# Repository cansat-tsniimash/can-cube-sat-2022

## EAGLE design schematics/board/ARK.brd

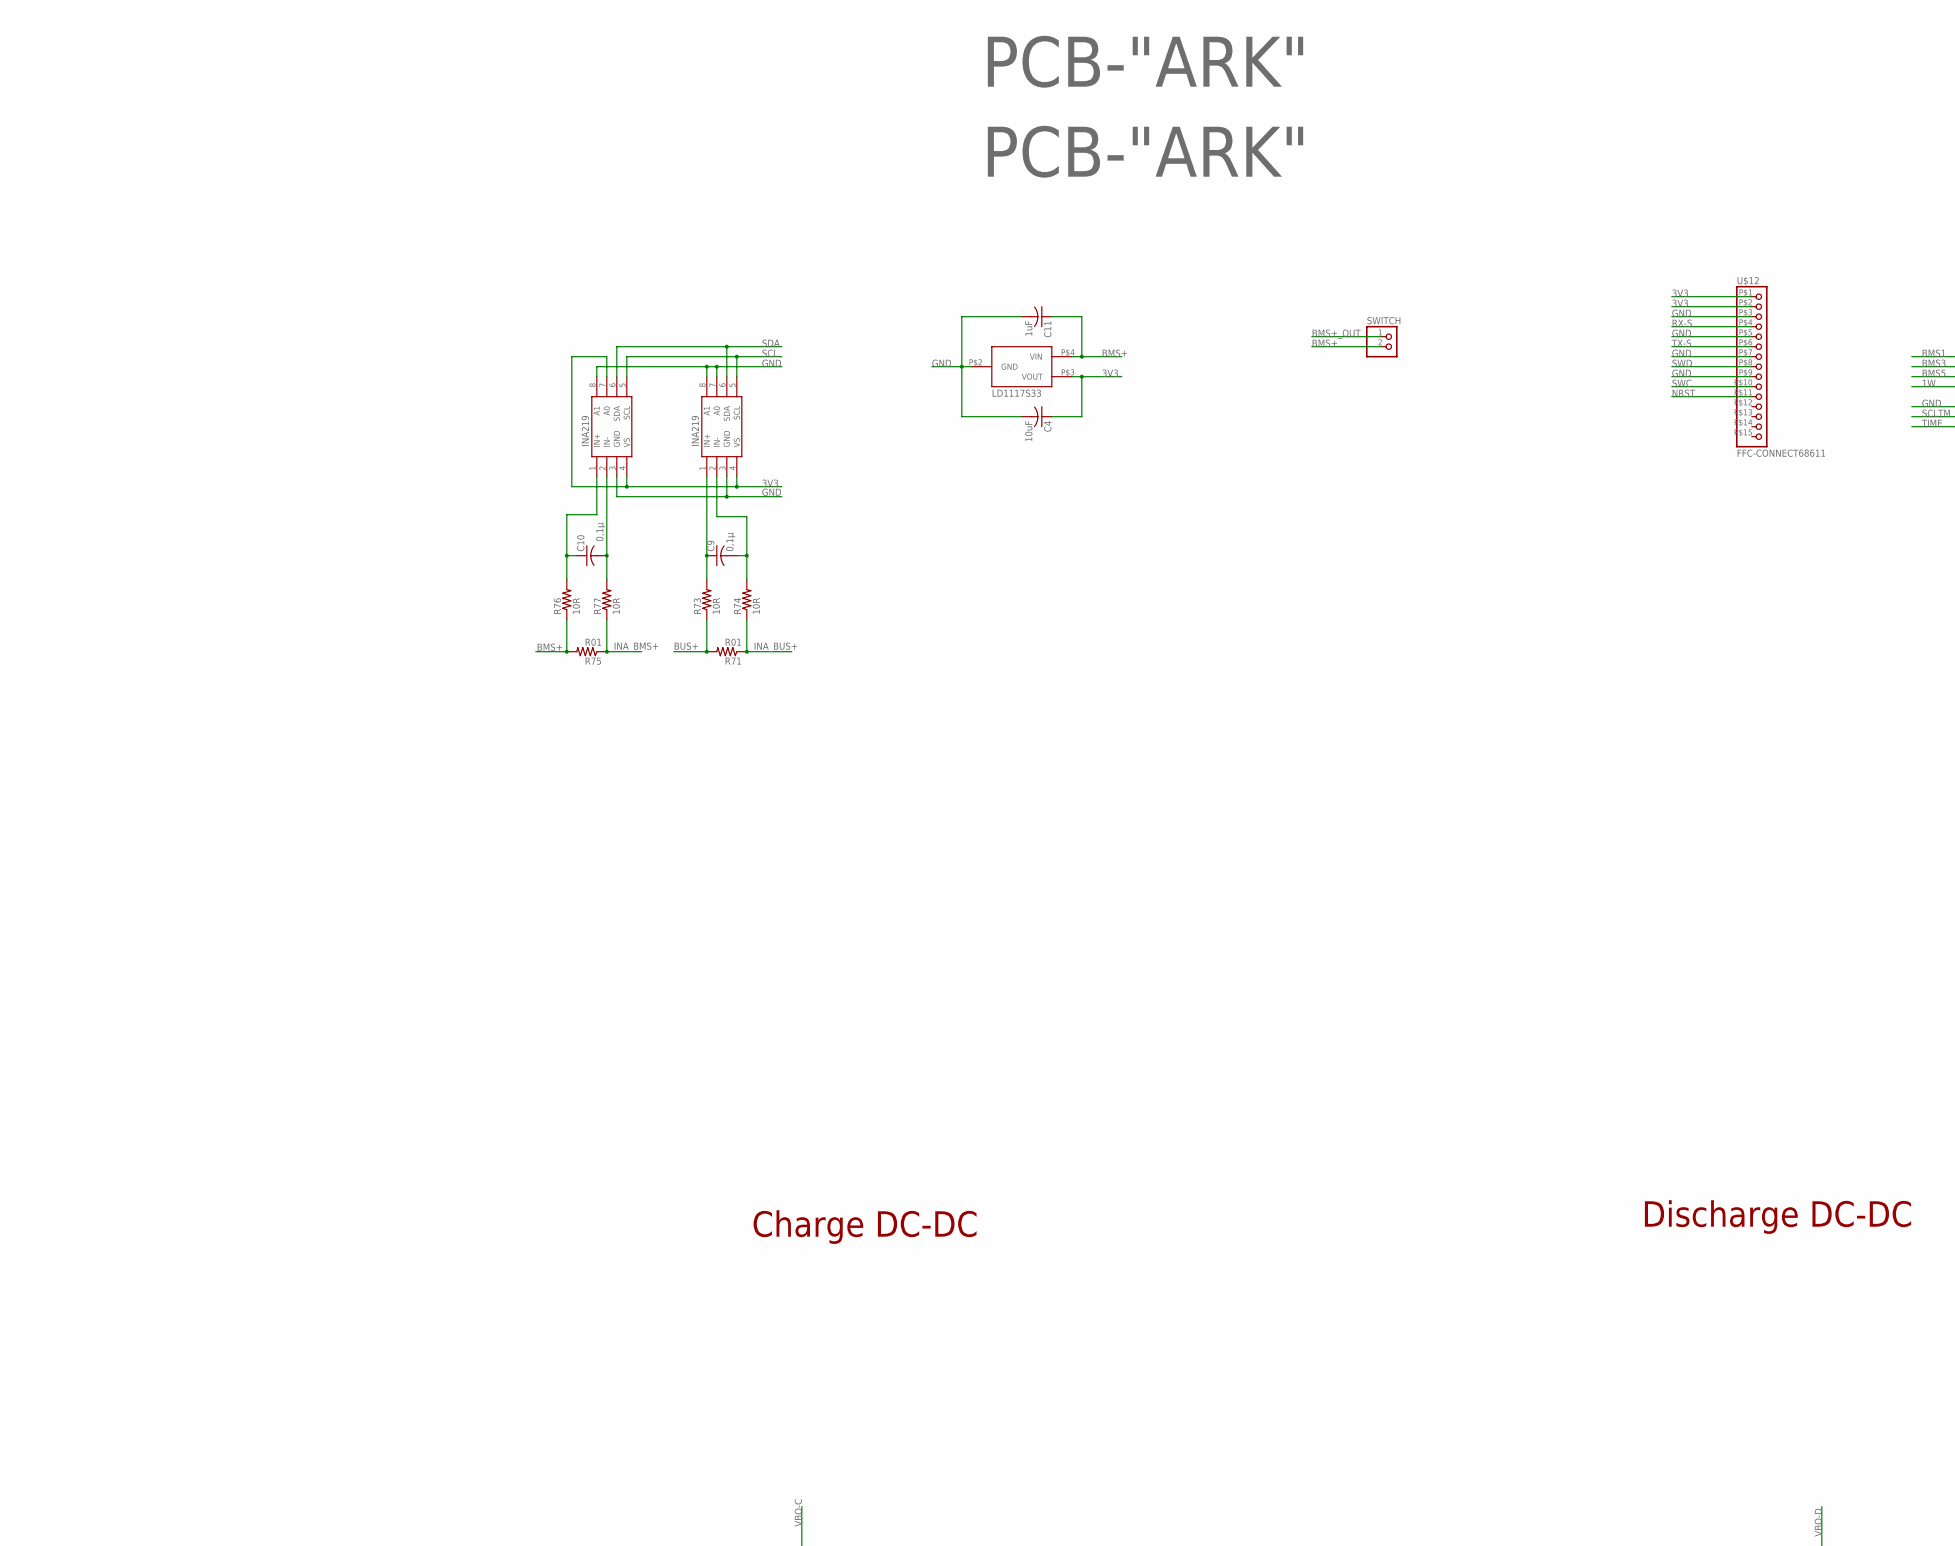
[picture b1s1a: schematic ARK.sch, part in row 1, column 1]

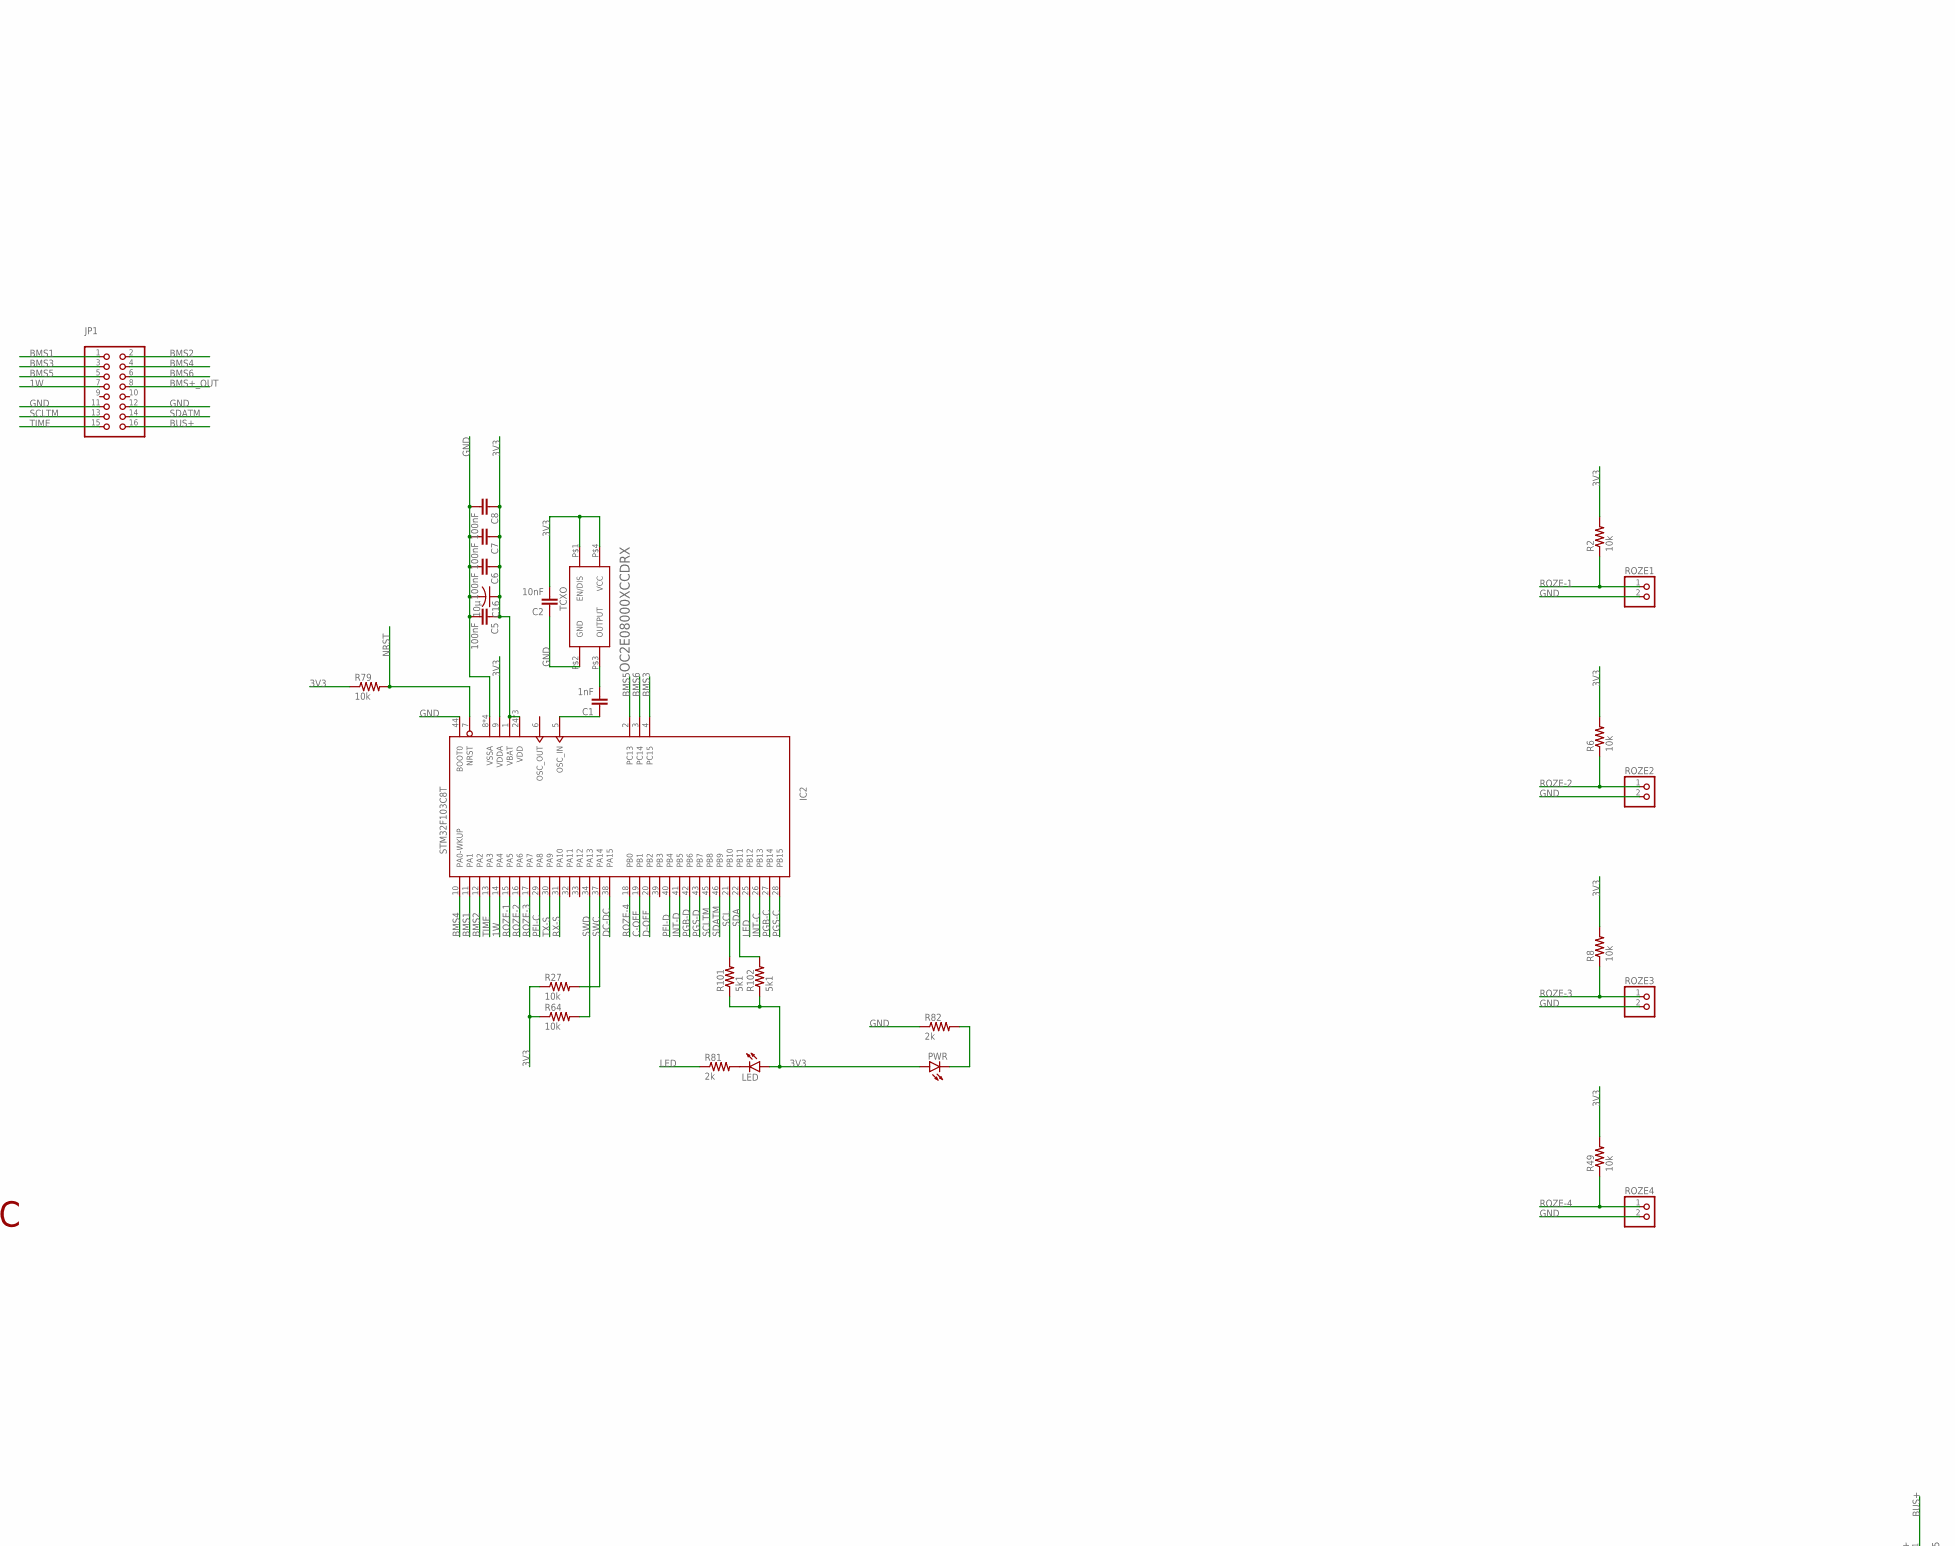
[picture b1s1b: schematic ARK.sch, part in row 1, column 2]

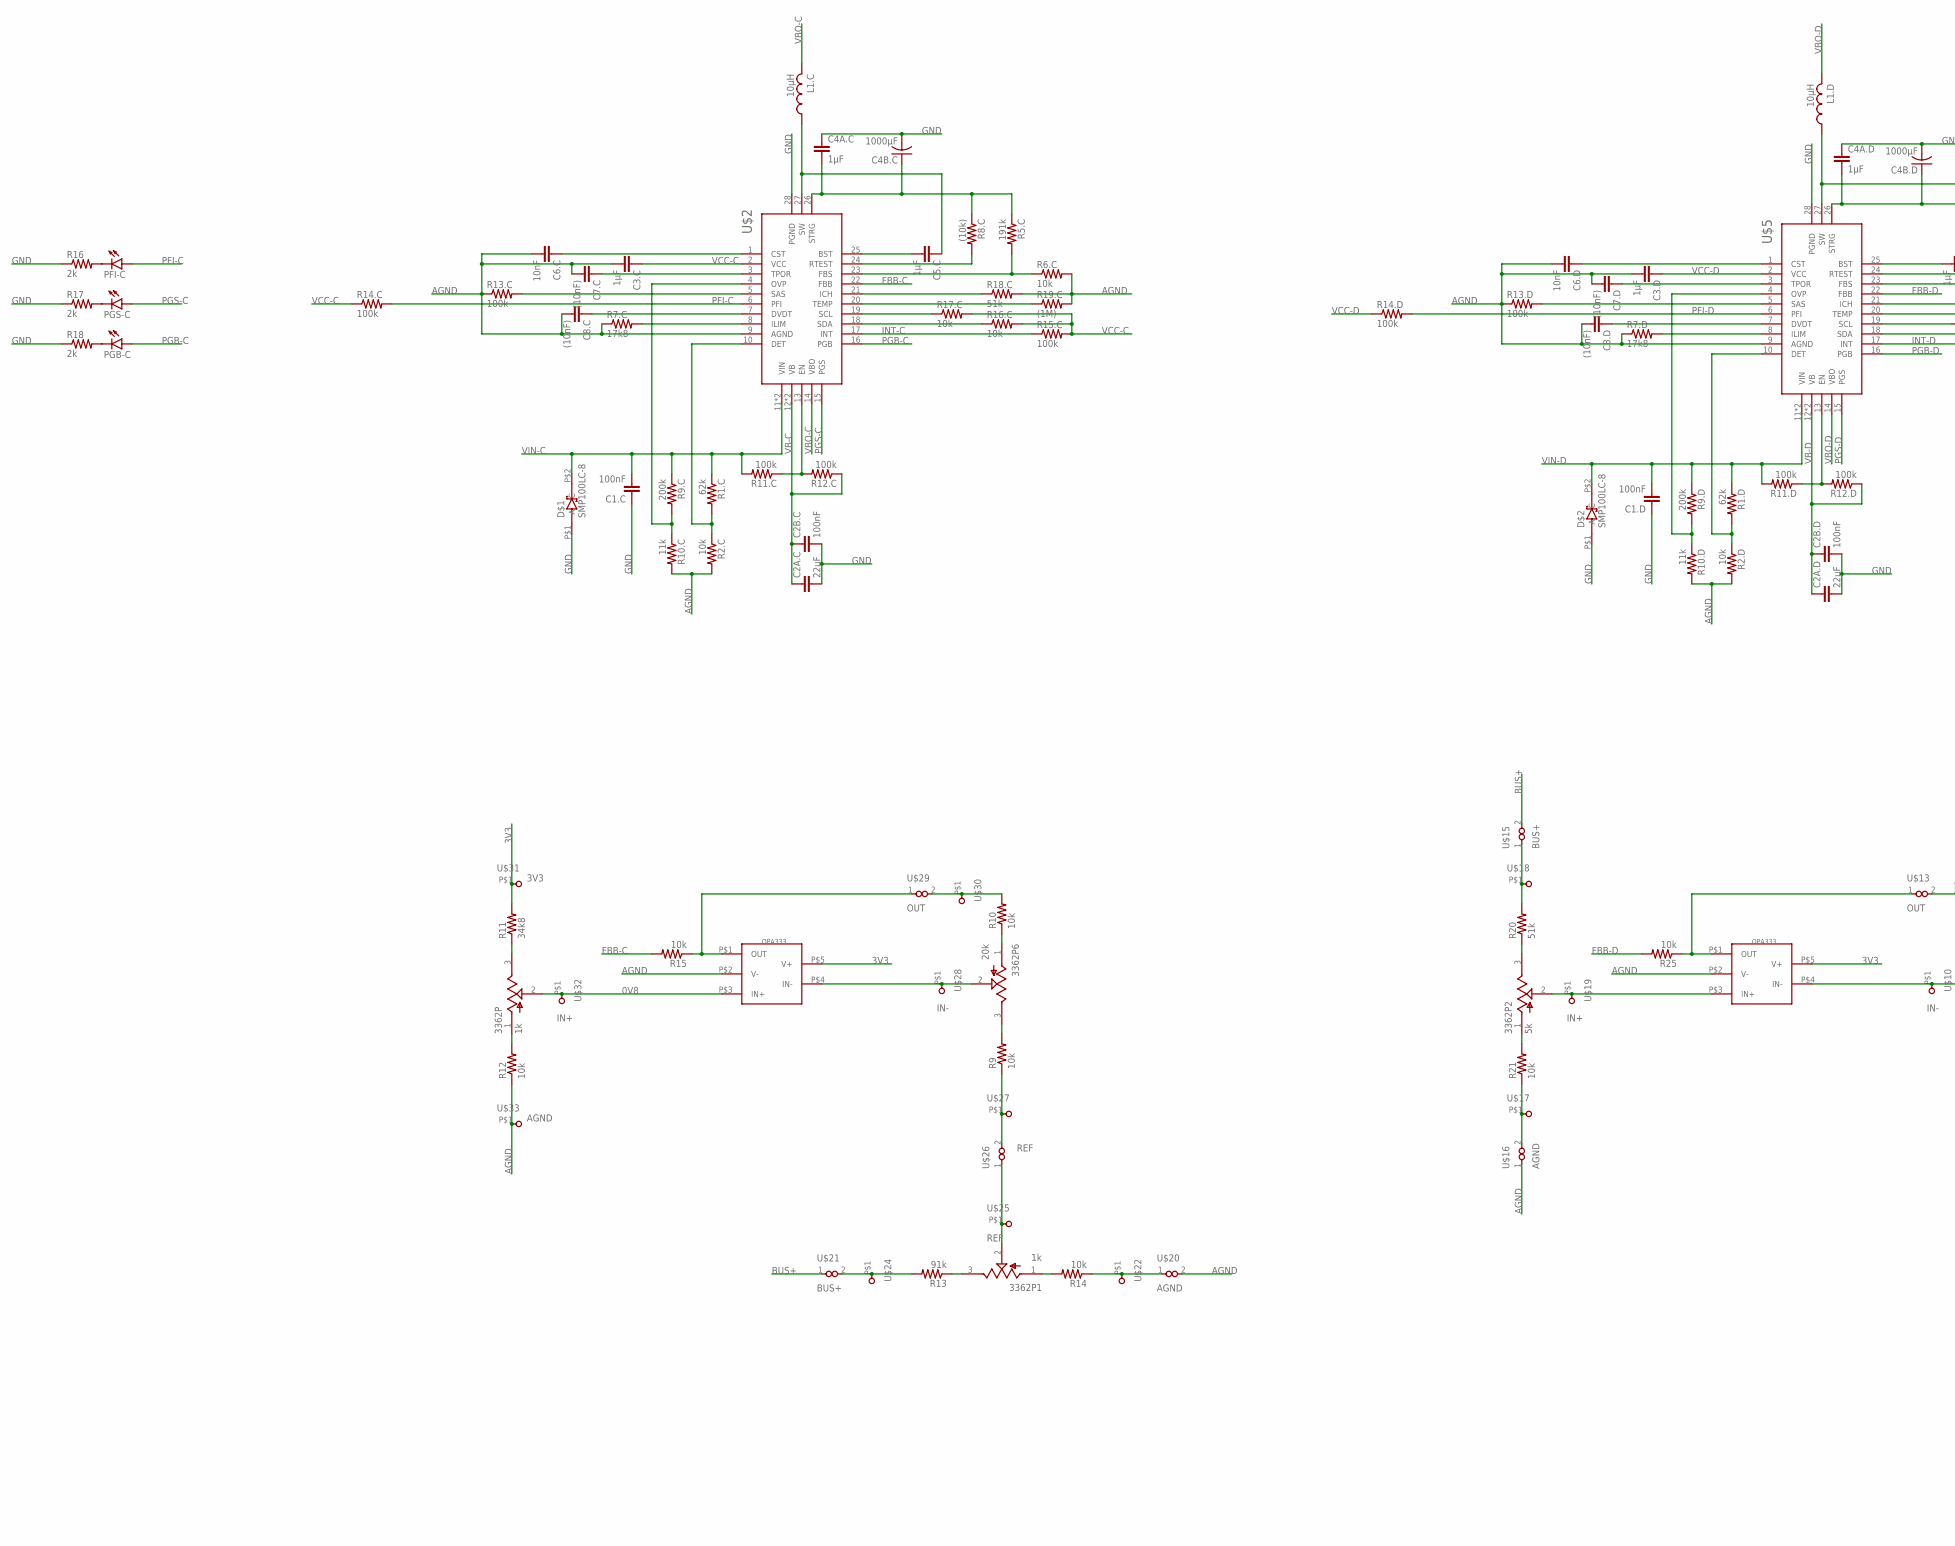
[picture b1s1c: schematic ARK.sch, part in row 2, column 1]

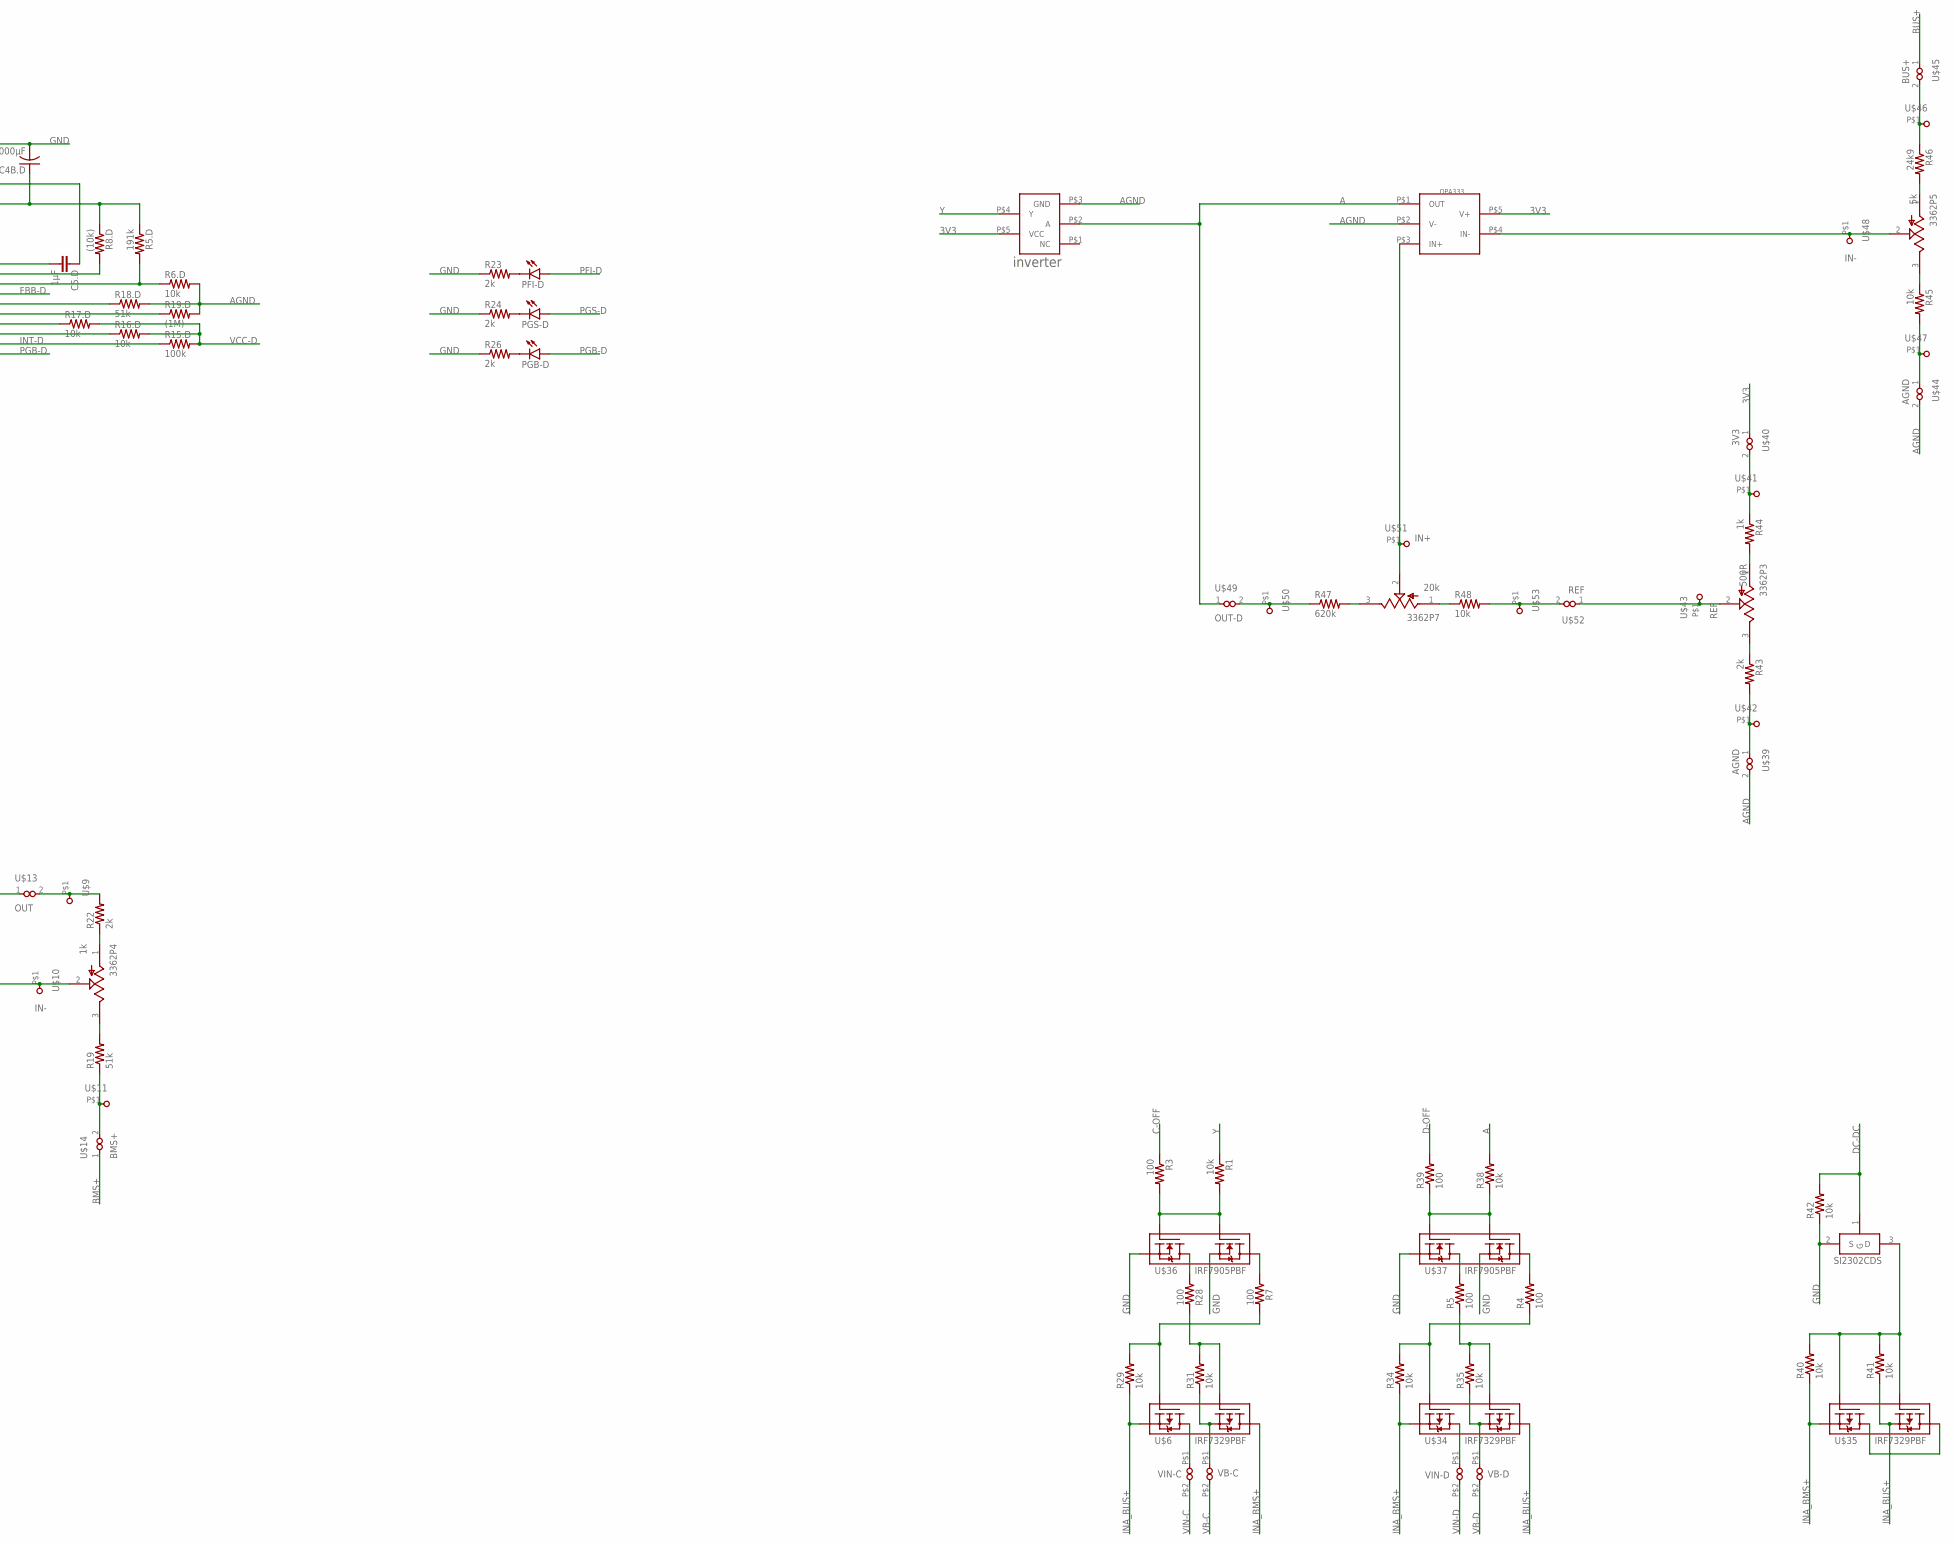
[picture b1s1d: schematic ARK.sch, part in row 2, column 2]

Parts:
3362P, 3362P1, 3362P4: 1k; TRIM_3362P-1-502LF
3362P2, 3362P5: 5k; TRIM_3362P-1-502LF
3362P3: 500R; TRIM_3362P-1-502LF
3362P6, 3362P7: 20k; TRIM_3362P-1-502LF
C1: 1nF; C0603
C1.C, C1.D, C2B.C, C2B.D, C5, C6, C7, C8: 100nF; C0603
C2, C6.C, C6.D: 10nF; C0603
C2A.C, C2A.D: 22µF; C1206
C3.C, C3.D, C5.C, C5.D: 1µF; C0603
C4: 10uF; ECAP-SMD-D4
C4A.C, C4A.D: 1µF; C1206
C4B.C, C4B.D: 1000µF; ECAP1000-CMD
C7.C, C7.D, C8.C, C8.D: (10nF); C0603
C9, C10: 0,1µ; C0603
C11: 1uF; ECAP-SMD-D4
C16: 10µ; C1206
D$1, D$2: SMP100LC-8; SMB
IC2: STM32F103C8T; LQFP48
INA219#1, INA219#2: INA219AID; SOT23-8
INVERT1: INVERTER.; SC70
JP1: PINHD-2X8; 2X08
L1.C, L1.D: 10µH; L_12X12
LD1117S33: LD1117S33; SOT223
LED: LEDCHIPLED_0603; CHIPLED_0603
OPA1, OPA2, OPA3: OPA333; SOT23-5
PFI-C: LEDCHIPLED_0603; CHIPLED_0603
PFI-D: LEDCHIPLED_0603; CHIPLED_0603
PGB-C: LEDCHIPLED_0603; CHIPLED_0603
PGB-D: LEDCHIPLED_0603; CHIPLED_0603
PGS-C: LEDCHIPLED_0603; CHIPLED_0603
PGS-D: LEDCHIPLED_0603; CHIPLED_0603
PWR: LEDCHIPLED_0603; CHIPLED_0603
R1, R2, R2.C, R2.D, R6, R6.C, R6.D, R8, R9, R10, R12, R14, R15, R16.C, R16.D, R17.C, R17.D, R21, R25, R27, R29, R31, R34, R35, R38, R40, R41, R42, R45, R48, R49, R64, R79: 10k; R0603
R1.C, R1.D: 62k; R0603
R3, R4, R5, R7, R28, R39: 100; R0603
R5.C, R5.D: 191k; R0603
R7.C, R7.D: 17k8; R0603
R8.C, R8.D: (10k); R0603
R9.C, R9.D: 200k; R0603
R10.C, R10.D: 11k; R0603
R11: 34k8; R0603
R11.C, R11.D, R12.C, R12.D, R13.C, R13.D, R14.C, R14.D, R15.C, R15.D: 100k; R0603
R13: 91k; R0603
R16, R17, R18, R22, R23, R24, R26, R43, R81, R82: 2k; R0603
R18.C, R18.D, R19, R20: 51k; R0603
R19.C, R19.D: (1M); R0603
R44: 1k; R0603
R46: 24k9; R0603
R47: 620k; R0603
R71, R75: R01; R2512
R73, R74, R76, R77: 10R; R0603
R101, R102: 5k1; R0603
ROZE1, ROZE2, ROZE3, ROZE4: PINHD-1X2; 1X02
SWITCH: PINHD-1X2; 1X02
TCXO: OC2E08000XCCDRX
U$1: VIN-C; SOLDERING-PAD-4A
U$2, U$5: MP5515; QFN-30
U$3, U$4: PCB-"ARK"; ITS-LOGO
U$6, U$34, U$35: IRF7329PBF; SO8
U$9, U$11, U$17, U$18, U$22, U$24, U$27, U$30, U$41, U$42, U$46, U$47, U$50, U$53: VIAS
U$10, U$28, U$48: IN-; VIAS
U$12: FFC-CONNECT68611; 68611
U$13, U$29: OUT; VIAS-CONNECT
U$14: BMS+; VIAS-CONNECT
U$15, U$21, U$45: BUS+; VIAS-CONNECT
U$16, U$20, U$39, U$44: AGND; VIAS-CONNECT
U$19, U$32, U$51: IN+; VIAS
U$23: VB-C; SOLDERING-PAD-4A
U$25, U$43: REF; VIAS
U$26, U$52: REF; VIAS-CONNECT
U$31: 3V3; VIAS
U$33: AGND; VIAS
U$36, U$37: IRF7905PBF; SO8
U$38: SI2302CDS; SOT23-3
U$40: 3V3; VIAS-CONNECT
U$49: OUT-D; VIAS-CONNECT
U$54: VIN-D; SOLDERING-PAD-4A
U$55: VB-D; SOLDERING-PAD-4A

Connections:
0V8: 3362P.2 (WIPER), OPA2.P$3 (IN+), U$32.P$1
1W: IC2.14 (PA4), JP1.7
3V3: C2.2, C4.P+ (1), C5.1, C6.1, C7.1, C8.1, C16.1, IC2.1 (VBAT), IC2.9 (VDDA), IC2.24 (VDD), IC2.36 (VDD), IC2.48 (VDD), INA219#1.4 (VS), INA219#2.4 (VS), INA219#2.7 (A0), INVERT1.P$5 (VCC), LD1117S33.P$3 (VOUT), LED.A, OPA1.P$5 (V+), OPA2.P$5 (V+), OPA3.P$5 (V+), PWR.A, R2.2, R6.2, R8.2, R11.2, R27.1, R49.2, R64.1, R79.1, R101.1, R102.1, TCXO.P$1 (EN/DIS), TCXO.P$4 (VCC), U$12.P$1 (1), U$12.P$2 (2), U$31.P$1, U$40.1
A: INVERT1.P$2 (A), OPA1.P$1 (OUT), R38.2, U$49.1
AGND: C3.C.2, C3.D.2, C6.C.2, C6.D.2, C7.C.2, C7.D.2, C8.C.2, C8.D.2, INVERT1.P$3 (GND), OPA1.P$2 (V-), OPA2.P$2 (V-), OPA3.P$2 (V-), R2.C.2, R2.D.2, R6.C.2, R6.D.2, R7.C.1, R7.D.1, R10.C.2, R10.D.2, R12.1, R13.C.1, R13.D.1, R18.C.2, R18.D.2, R19.C.2, R19.D.2, U$2.9 (AGND), U$5.9 (AGND), U$16.1, U$20.2, U$33.P$1, U$39.2, U$44.2; also elsewhere on the board
BMS1: IC2.11 (PA1), JP1.1
BMS2: IC2.12 (PA2), JP1.2
BMS3: IC2.4 (PC15), JP1.3
BMS4: IC2.10 (PA0-WKUP), JP1.4
BMS5: IC2.2 (PC13), JP1.5
BMS6: IC2.3 (PC14), JP1.6
BMS+: C11.P+ (1), LD1117S33.P$4 (VIN), R75.2, R76.1, SWITCH.2, U$14.1
BMS+_OUT: JP1.8, SWITCH.1
BUS+: JP1.16, R71.2, R73.1, U$15.2, U$21.1, U$45.1
C-OFF: IC2.19 (PB1), R3.1
D-OFF: IC2.20 (PB2), R39.2
DC-DC: IC2.38 (PA15), R42.2, U$38.1 (G)
FBB-C: R15.2, U$2.22 (FBB)
FBB-D: R25.2, U$5.22 (FBB)
GND: C1.C.1, C1.D.1, C2.1, C2A.C.2, C2A.D.2, C2B.C.2, C2B.D.2, C4.P- (2), C4A.C.1, C4A.D.1, C4B.C.P$2 (2), C4B.D.P$2 (2), C5.2, C6.2, C7.2, C8.2, C11.P- (2), C16.2, D$1.P$1 (A), D$2.P$1 (A), IC2.8 (VSSA), IC2.23 (VSSA), IC2.35 (VSSA), IC2.44 (BOOT0), IC2.47 (VSSA), INA219#1.3 (GND), INA219#1.7 (A0), INA219#1.8 (A1), INA219#2.3 (GND), INA219#2.8 (A1), JP1.11, JP1.12, LD1117S33.P$2 (GND), R16.1, R17.1, R18.1, R23.1, R24.1, R26.1, R42.1, R82.1, ROZE1.2, ROZE2.2, ROZE3.2, ROZE4.2, TCXO.P$2 (GND), U$2.28 (PGND), U$5.28 (PGND), U$12.P$3 (3), U$12.P$5 (5), U$12.P$7 (7), U$12.P$9 (9), U$36.1 (S2), U$36.3 (S1), U$37.1 (S2), U$37.3 (S1), U$38.2 (S); also elsewhere on the board
INA_BMS+: R34.1, R40.1, R75.1, R77.1, U$6.7 (D1), U$6.8 (D1), U$34.3 (S2), U$35.3 (S2)
INA_BUS+: R29.1, R41.1, R71.1, R74.1, U$6.3 (S2), U$34.7 (D1), U$34.8 (D1), U$35.1 (S1)
INT-C: IC2.26 (PB13), R15.C.1, U$2.17 (INT)
INT-D: IC2.41 (PB5), R15.D.1, U$5.17 (INT)
LED: IC2.25 (PB12), R81.1
unnamed: C1.1, IC2.5 (OSC_IN)
unnamed: U$1.P$1 (1), U$6.5 (D2), U$6.6 (D2)
unnamed: R31.1, U$6.1 (S1), U$23.P$1 (1)
unnamed: C1.2, TCXO.P$3 (OUTPUT)
unnamed: R4.1, R34.2, U$34.4 (G2)
unnamed: OPA3.P$1 (OUT), R25.1, U$13.1
unnamed: R11.C.1, R12.C.2, U$2.13 (EN)
unnamed: R7.C.2, U$2.8 (ILIM)
unnamed: C7.C.1, U$2.3 (TPOR)
unnamed: R1.C.2, R2.C.1, U$2.10 (DET)
unnamed: R9.C.2, R10.C.1, U$2.4 (OVP)
unnamed: C8.C.1, U$2.7 (DVDT)
unnamed: R18.C.1, U$2.21 (ICH)
unnamed: C9.2, INA219#1.2 (IN-), R74.2
unnamed: R19.C.1, U$2.20 (TEMP)
unnamed: R13.C.2, U$2.5 (SAS)
unnamed: LED.C, R81.2
unnamed: C6.C.1, U$2.1 (CST)
unnamed: C4A.C.2, C4B.C.P$1 (1), R5.C.1, R8.C.1, U$2.26 (STRG)
unnamed: C5.C.2, U$2.25 (BST)
unnamed: C5.C.1, L1.C.P$1 (1), U$2.27 (SW)
unnamed: R5.C.2, R6.C.1, U$2.23 (FBS)
unnamed: R8.C.2, U$2.24 (RTEST)
unnamed: 3362P4.1 (CCW), R22.1
unnamed: R7.2, R29.2, U$6.4 (G2)
unnamed: R17.C.1, U$2.19 (SCL)
unnamed: R16.C.1, U$2.18 (SDA)
unnamed: R5.1, R35.2, U$34.2 (G1)
unnamed: 3362P2.2 (WIPER), OPA3.P$3 (IN+), U$19.P$1
unnamed: R11.D.1, R12.D.2, U$5.13 (EN)
unnamed: R1.D.2, R2.D.1, U$5.10 (DET)
unnamed: R9.D.2, R10.D.1, U$5.4 (OVP)
unnamed: R7.D.2, U$5.8 (ILIM)
unnamed: C7.D.1, U$5.3 (TPOR)
unnamed: C8.D.1, U$5.7 (DVDT)
unnamed: R18.D.1, U$5.21 (ICH)
unnamed: R19.D.1, U$5.20 (TEMP)
unnamed: R13.D.2, U$5.5 (SAS)
unnamed: C6.D.1, U$5.1 (CST)
unnamed: C5.D.2, U$5.25 (BST)
unnamed: C5.D.1, L1.D.P$1 (1), U$5.27 (SW)
unnamed: R5.D.2, R6.D.1, U$5.23 (FBS)
unnamed: R8.D.2, U$5.24 (RTEST)
unnamed: C4A.D.2, C4B.D.P$1 (1), R5.D.1, R8.D.1, U$5.26 (STRG)
unnamed: U$35.5 (D2), U$35.6 (D2), U$35.7 (D1), U$35.8 (D1)
unnamed: R17.D.1, U$5.19 (SCL)
unnamed: R1.2, R3.2, U$36.2 (G2), U$36.4 (G1)
unnamed: R16.D.1, U$5.18 (SDA)
unnamed: U$34.5 (D2), U$34.6 (D2), U$54.P$1 (1)
unnamed: R38.1, R39.1, U$37.2 (G2), U$37.4 (G1)
unnamed: OPA2.P$1 (OUT), R15.1, U$29.1
unnamed: 3362P6.2 (WIPER), OPA2.P$4 (IN-), U$28.P$1
unnamed: 3362P6.3 (CW), R9.2
unnamed: 3362P6.1 (CCW), R10.1
unnamed: PFI-C.C, R16.2
unnamed: 3362P.3 (CW), R11.1
unnamed: 3362P.1 (CCW), R12.2
unnamed: 3362P1.3 (CW), R13.1
unnamed: 3362P1.1 (CCW), R14.2
unnamed: 3362P1.2 (WIPER), U$25.P$1, U$26.1
unnamed: 3362P2.3 (CW), R20.1
unnamed: PGS-C.C, R17.2
unnamed: 3362P2.1 (CCW), R21.2
unnamed: PGB-C.C, R18.2
unnamed: 3362P4.2 (WIPER), OPA3.P$4 (IN-), U$10.P$1
unnamed: 3362P4.3 (CW), R19.2
unnamed: PFI-D.C, R23.2
unnamed: PGS-D.C, R24.2
unnamed: PGB-D.C, R26.2
unnamed: R22.2, U$9.P$1, U$13.2
unnamed: R19.1, U$11.P$1, U$14.2
unnamed: R20.2, U$15.1, U$18.P$1
unnamed: R21.1, U$16.2, U$17.P$1
unnamed: R13.2, U$21.2, U$24.P$1
unnamed: R14.1, U$20.1, U$22.P$1
unnamed: R35.1, U$34.1 (S1), U$55.P$1 (1)
unnamed: R5.2, U$37.7 (D2), U$37.8 (D2)
unnamed: R28.1, U$36.7 (D2), U$36.8 (D2)
unnamed: R4.2, U$37.5 (D1), U$37.6 (D1)
unnamed: R7.1, U$36.5 (D1), U$36.6 (D1)
unnamed: R9.1, U$26.2, U$27.P$1
unnamed: R10.2, U$29.2, U$30.P$1
unnamed: R28.2, R31.2, U$6.2 (G1)
unnamed: 3362P3.3 (CW), R43.1
unnamed: 3362P3.1 (CCW), R44.2
unnamed: 3362P3.2 (WIPER), U$43.P$1, U$52.1
unnamed: R40.2, R41.2, U$35.2 (G1), U$35.4 (G2), U$38.3 (D)
unnamed: R43.2, U$39.1, U$42.P$1
unnamed: R44.1, U$40.2, U$41.P$1
unnamed: 3362P5.3 (CW), R45.1
unnamed: 3362P5.1 (CCW), R46.2
unnamed: 3362P5.2 (WIPER), OPA1.P$4 (IN-), U$48.P$1
unnamed: R45.2, U$44.1, U$47.P$1
unnamed: R46.1, U$45.2, U$46.P$1
unnamed: 3362P7.1 (CCW), R48.1
unnamed: 3362P7.2 (WIPER), OPA1.P$3 (IN+), U$51.P$1
unnamed: 3362P7.3 (CW), R47.2
unnamed: R47.1, U$49.2, U$50.P$1
unnamed: R48.2, U$52.2, U$53.P$1
unnamed: C9.1, INA219#1.1 (IN+), R73.2
unnamed: C10.1, INA219#2.1 (IN+), R76.2
unnamed: C10.2, INA219#2.2 (IN-), R77.2
unnamed: PWR.C, R82.2
NRST: IC2.7 (NRST), R79.2, U$12.P$11 (11)
PFI-C: IC2.29 (PA8), PFI-C.A, R14.C.2, U$2.6 (PFI)
PFI-D: IC2.40 (PB4), PFI-D.A, R14.D.2, U$5.6 (PFI)
PGB-C: IC2.27 (PB14), PGB-C.A, U$2.16 (PGB)
PGB-D: IC2.42 (PB6), PGB-D.A, U$5.16 (PGB)
PGS-C: IC2.28 (PB15), PGS-C.A, U$2.15 (PGS)
PGS-D: IC2.43 (PB7), PGS-D.A, U$5.15 (PGS)
ROZE-1: IC2.15 (PA5), R2.1, ROZE1.1
ROZE-2: IC2.16 (PA6), R6.1, ROZE2.1
ROZE-3: IC2.17 (PA7), R8.1, ROZE3.1
ROZE-4: IC2.18 (PB0), R49.1, ROZE4.1
RX-S: IC2.31 (PA10), U$12.P$4 (4)
SCL: IC2.21 (PB10), INA219#1.5 (SCL), INA219#2.5 (SCL), R101.2
SCLTM: IC2.45 (PB8), JP1.13
SDA: IC2.22 (PB11), INA219#1.6 (SDA), INA219#2.6 (SDA), R102.2
SDATM: IC2.46 (PB9), JP1.14
SWC: IC2.37 (PA14), R27.2, U$12.P$10 (10)
SWD: IC2.34 (PA13), R64.2, U$12.P$8 (8)
TIME: IC2.13 (PA3), JP1.15
TX-S: IC2.30 (PA9), U$12.P$6 (6)
VB-C: C2A.C.1, C2B.C.1, R12.C.1, U$2.12 (VB), U$2.29 (VB), U$23.P$2 (2)
VB-D: C2A.D.1, C2B.D.1, R12.D.1, U$5.12 (VB), U$5.29 (VB), U$55.P$2 (2)
VBO-C: L1.C.P$2 (2), U$2.14 (VBO)
VBO-D: L1.D.P$2 (2), U$5.14 (VBO)
VCC-C: C3.C.1, R14.C.1, R15.C.2, R16.C.2, R17.C.2, U$2.2 (VCC)
VCC-D: C3.D.1, R14.D.1, R15.D.2, R16.D.2, R17.D.2, U$5.2 (VCC)
VIN-C: C1.C.2, D$1.P$2 (C), R1.C.1, R9.C.1, R11.C.2, U$1.P$2 (2), U$2.11 (VIN), U$2.30 (VIN)
VIN-D: C1.D.2, D$2.P$2 (C), R1.D.1, R9.D.1, R11.D.2, U$5.11 (VIN), U$5.30 (VIN), U$54.P$2 (2)
Y: INVERT1.P$4 (Y), R1.1

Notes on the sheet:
Charge DC-DC
Discharge DC-DC

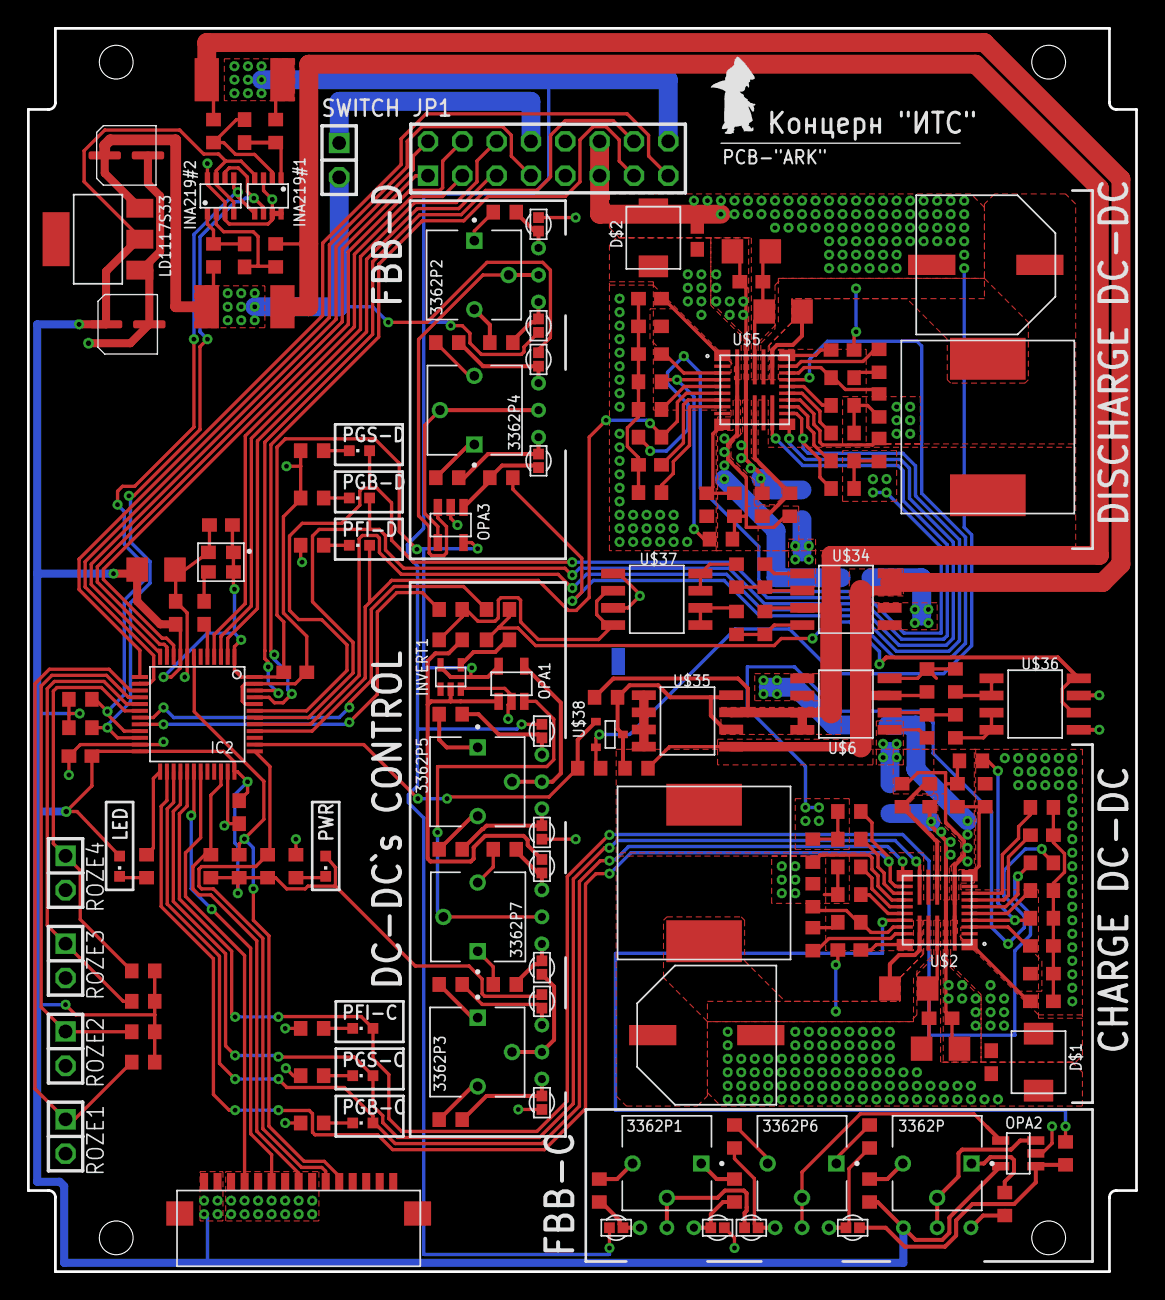
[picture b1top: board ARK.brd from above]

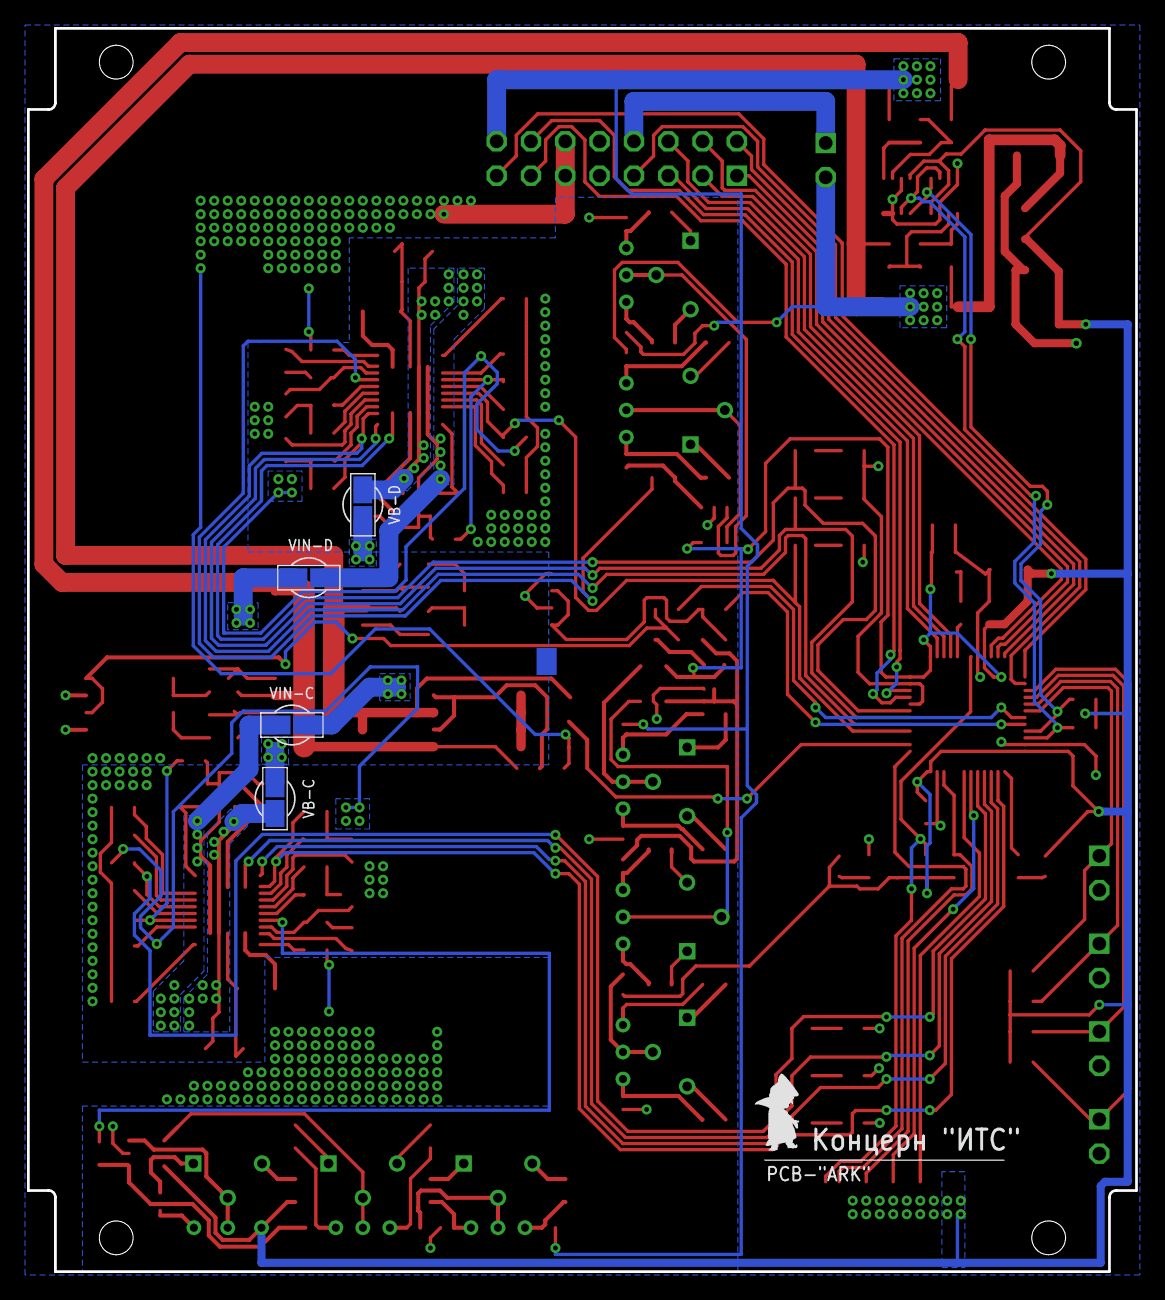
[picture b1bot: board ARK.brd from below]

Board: 2 copper layers, 82.0 x 92.0 mm, 210 parts (6 on the bottom side), 157 nets.

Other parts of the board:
U$7: GNDS-CONNECTOR

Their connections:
AGND: U$7.P$2; also elsewhere on the board
GND: U$7.P$1; also elsewhere on the board

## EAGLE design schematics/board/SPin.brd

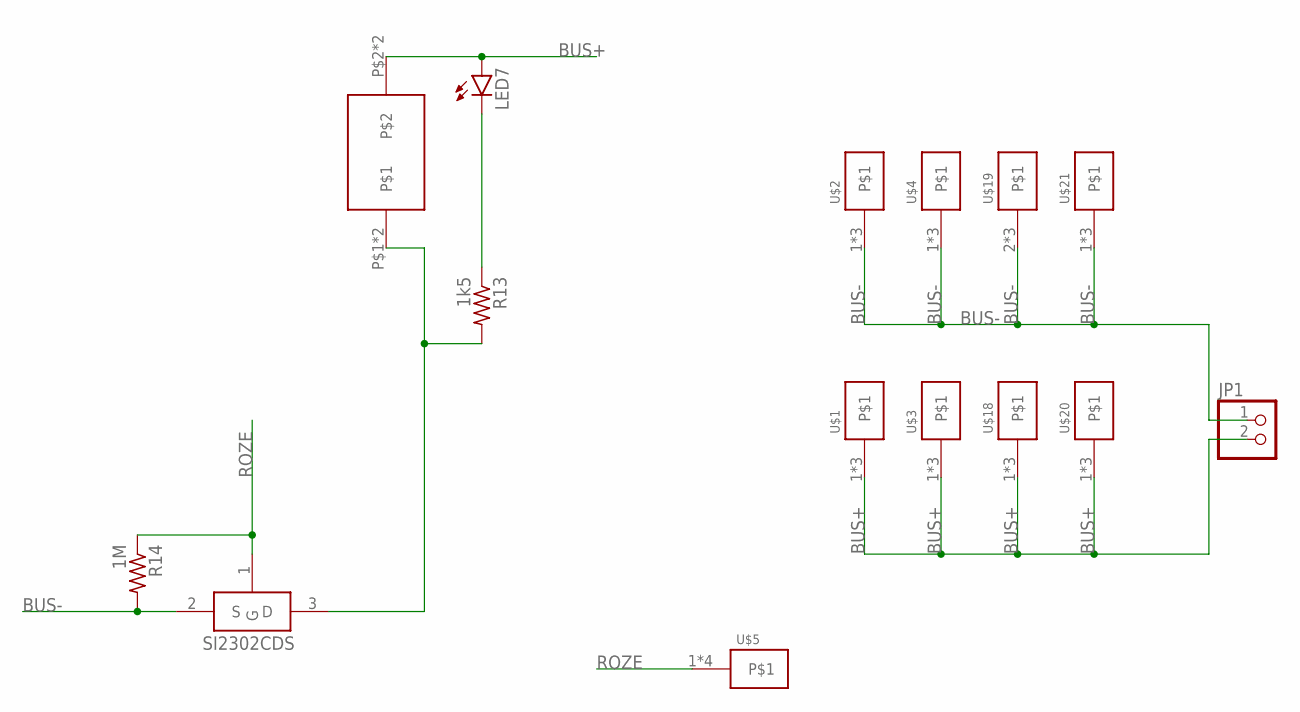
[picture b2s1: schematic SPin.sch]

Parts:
JP1: PINHD-1X2; 1X02
LED7: LEDCHIPLED_0603; CHIPLED_0603
R13: 1k5; R0603
R14: 1M; R0603
U$1, U$2, U$20, U$21: KCONNECT3; KCONNECT-3
U$3, U$4, U$18: KCONNECT4; KCONNECT-4
U$5: KCONNECTQUAD-; KCONNECT-_QUAD
U$6: GRAFITGRAFIT4_2; GRAFIT4_2
U$13: SI2302CDS; SOT23-3
U$19: KCONNECT1; KCONNECT-1

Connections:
2: R13.2, U$6.P$1, U$6.P$4, U$13.3 (D)
BUS+: JP1.2, LED7.A, U$1.1, U$1.2, U$1.4, U$3.1, U$3.2, U$3.3, U$6.P$2, U$6.P$5, U$18.1, U$18.2, U$18.3, U$20.1, U$20.2, U$20.4
BUS-: JP1.1, R14.2, U$2.1, U$2.2, U$2.4, U$4.1, U$4.2, U$4.3, U$13.2 (S), U$19.2, U$19.3, U$19.4, U$21.1, U$21.2, U$21.4
unnamed: LED7.C, R13.1
ROZE: R14.1, U$5.1, U$5.2, U$5.3, U$5.4, U$13.1 (G)
